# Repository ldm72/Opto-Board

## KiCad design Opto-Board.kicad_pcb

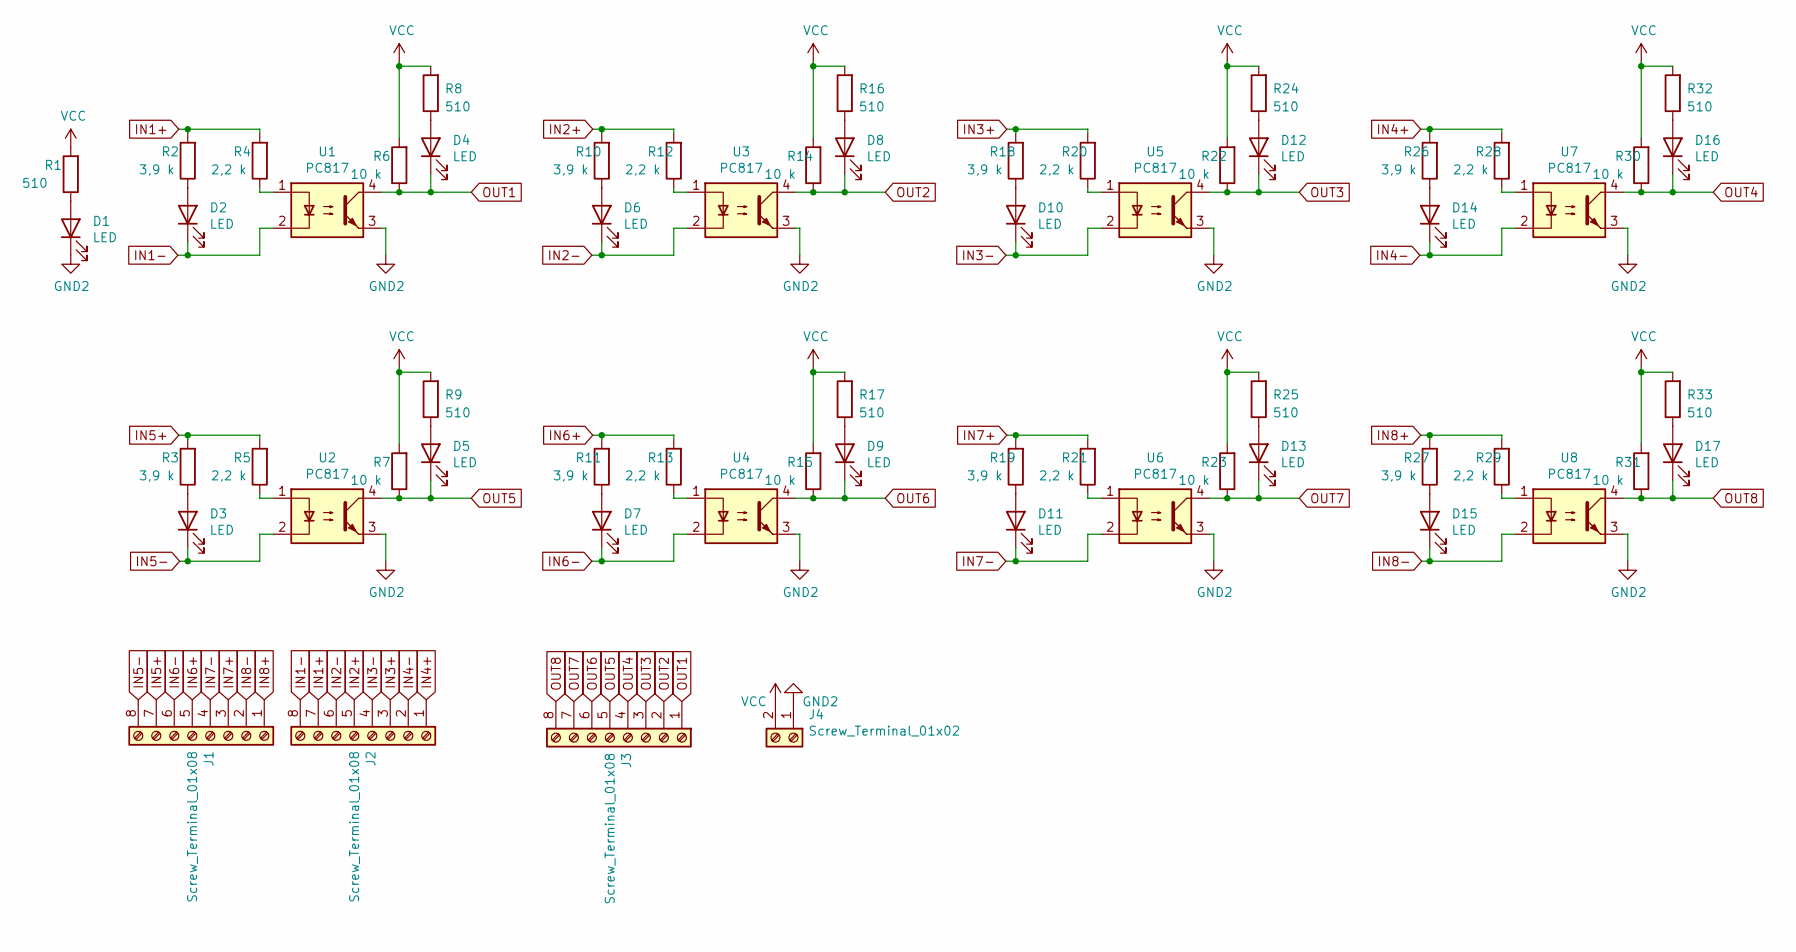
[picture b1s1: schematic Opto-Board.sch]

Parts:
D1, D2, D3, D4, D5, D6, D7, D8, D9, D10, D11, D12, D13, D14, D15, D16, D17: LED; LED_D3.0mm
J1, J2, J3: Screw_Terminal_01x08; TerminalBlock_Phoenix_MKDS-1,5-8_1x08_P5.00mm_Horizontal
J4: Screw_Terminal_01x02; TerminalBlock_Phoenix_MKDS-1,5-2_1x02_P5.00mm_Horizontal
R1, R8, R9, R16, R17, R24, R25, R32, R33: 510; R_1206_3216Metric_Pad1.42x1.75mm_HandSolder
R2, R3, R10, R11, R18, R19, R26, R27: 3,9 k; R_1206_3216Metric_Pad1.42x1.75mm_HandSolder
R4, R5, R12, R13, R20, R21, R28, R29: 2,2 k; R_1206_3216Metric_Pad1.42x1.75mm_HandSolder
R6, R7, R14, R15, R22, R23, R30, R31: 10 k; R_1206_3216Metric_Pad1.42x1.75mm_HandSolder
U1, U2, U3, U4, U5, U6, U7, U8: PC817; DIP-4_W7.62mm

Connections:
GND2: D1.1 (K), J4.1, U1.3, U2.3, U3.3, U4.3, U5.3, U6.3, U7.3, U8.3
IN1+: J2.7, R2.2, R4.2
IN1-: D2.1 (K), J2.8, U1.2
IN2+: J2.5, R10.2, R12.2
IN2-: D6.1 (K), J2.6, U3.2
IN3+: J2.3, R18.2, R20.2
IN3-: D10.1 (K), J2.4, U5.2
IN4+: J2.1, R26.2, R28.2
IN4-: D14.1 (K), J2.2, U7.2
IN5+: J1.7, R3.2, R5.2
IN5-: D3.1 (K), J1.8, U2.2
IN6+: J1.5, R11.2, R13.2
IN6-: D7.1 (K), J1.6, U4.2
IN7+: J1.3, R19.2, R21.2
IN7-: D11.1 (K), J1.4, U6.2
IN8+: J1.1, R27.2, R29.2
IN8-: D15.1 (K), J1.2, U8.2
unnamed: D1.2 (A), R1.1
unnamed: D2.2 (A), R2.1
unnamed: D3.2 (A), R3.1
unnamed: D4.2 (A), R8.1
unnamed: D5.2 (A), R9.1
unnamed: D6.2 (A), R10.1
unnamed: D7.2 (A), R11.1
unnamed: D8.2 (A), R16.1
unnamed: D9.2 (A), R17.1
unnamed: D10.2 (A), R18.1
unnamed: D11.2 (A), R19.1
unnamed: D12.2 (A), R24.1
unnamed: D13.2 (A), R25.1
unnamed: D14.2 (A), R26.1
unnamed: D15.2 (A), R27.1
unnamed: D16.2 (A), R32.1
unnamed: D17.2 (A), R33.1
unnamed: R4.1, U1.1
unnamed: R5.1, U2.1
unnamed: R12.1, U3.1
unnamed: R13.1, U4.1
unnamed: R20.1, U5.1
unnamed: R21.1, U6.1
unnamed: R28.1, U7.1
unnamed: R29.1, U8.1
OUT1: D4.1 (K), J3.1, R6.1, U1.4
OUT2: D8.1 (K), J3.2, R14.1, U3.4
OUT3: D12.1 (K), J3.3, R22.1, U5.4
OUT4: D16.1 (K), J3.4, R30.1, U7.4
OUT5: D5.1 (K), J3.5, R7.1, U2.4
OUT6: D9.1 (K), J3.6, R15.1, U4.4
OUT7: D13.1 (K), J3.7, R23.1, U6.4
OUT8: D17.1 (K), J3.8, R31.1, U8.4
VCC: J4.2, R1.2, R6.2, R7.2, R8.2, R9.2, R14.2, R15.2, R16.2, R17.2, R22.2, R23.2, R24.2, R25.2, R30.2, R31.2, R32.2, R33.2

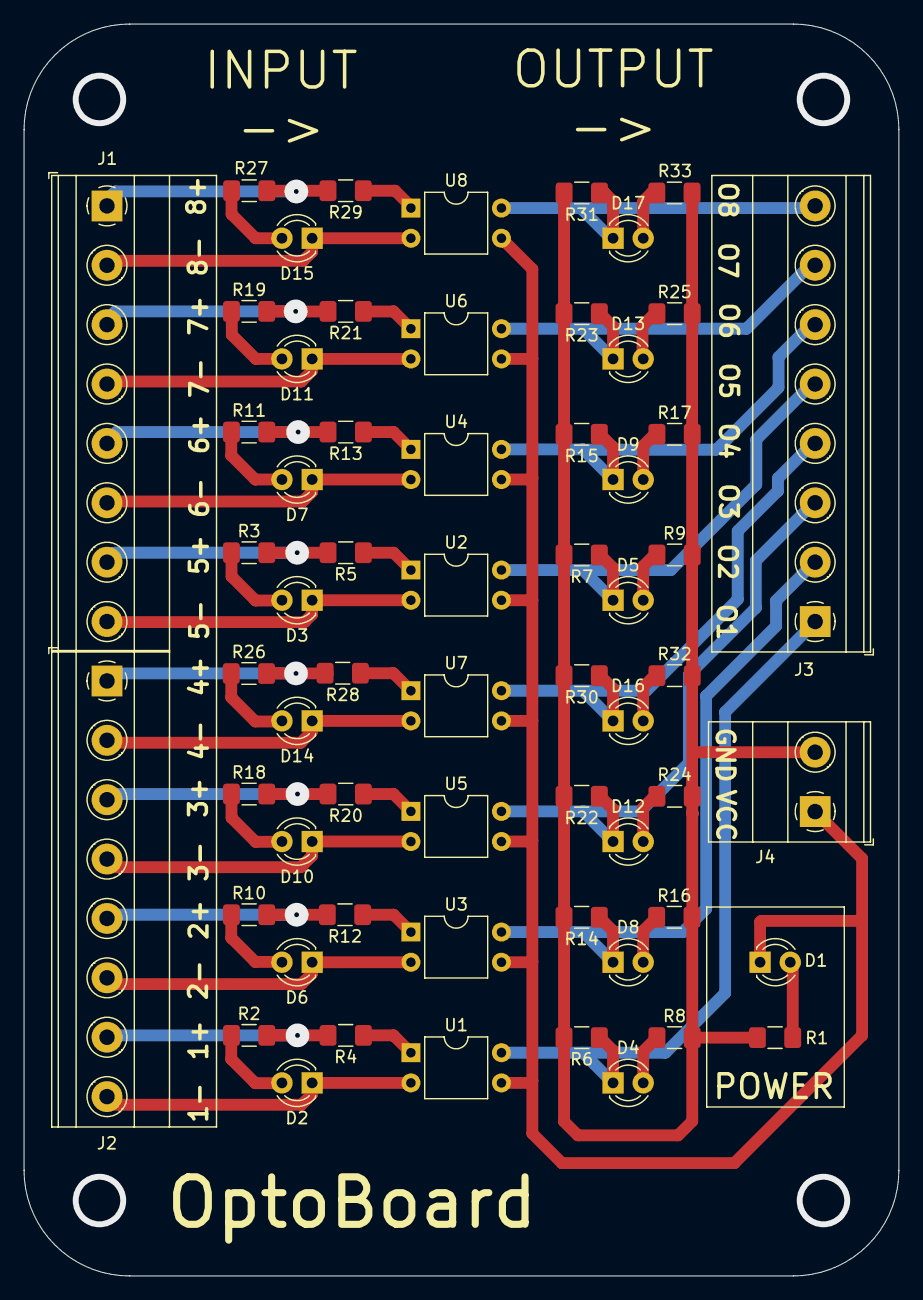
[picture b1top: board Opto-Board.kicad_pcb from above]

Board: 2 copper layers, 73.7 x 105.4 mm, 62 parts (0 on the bottom side), 51 nets.

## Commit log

2020-10-25 Some fixes
2020-10-26 More fixes + export
